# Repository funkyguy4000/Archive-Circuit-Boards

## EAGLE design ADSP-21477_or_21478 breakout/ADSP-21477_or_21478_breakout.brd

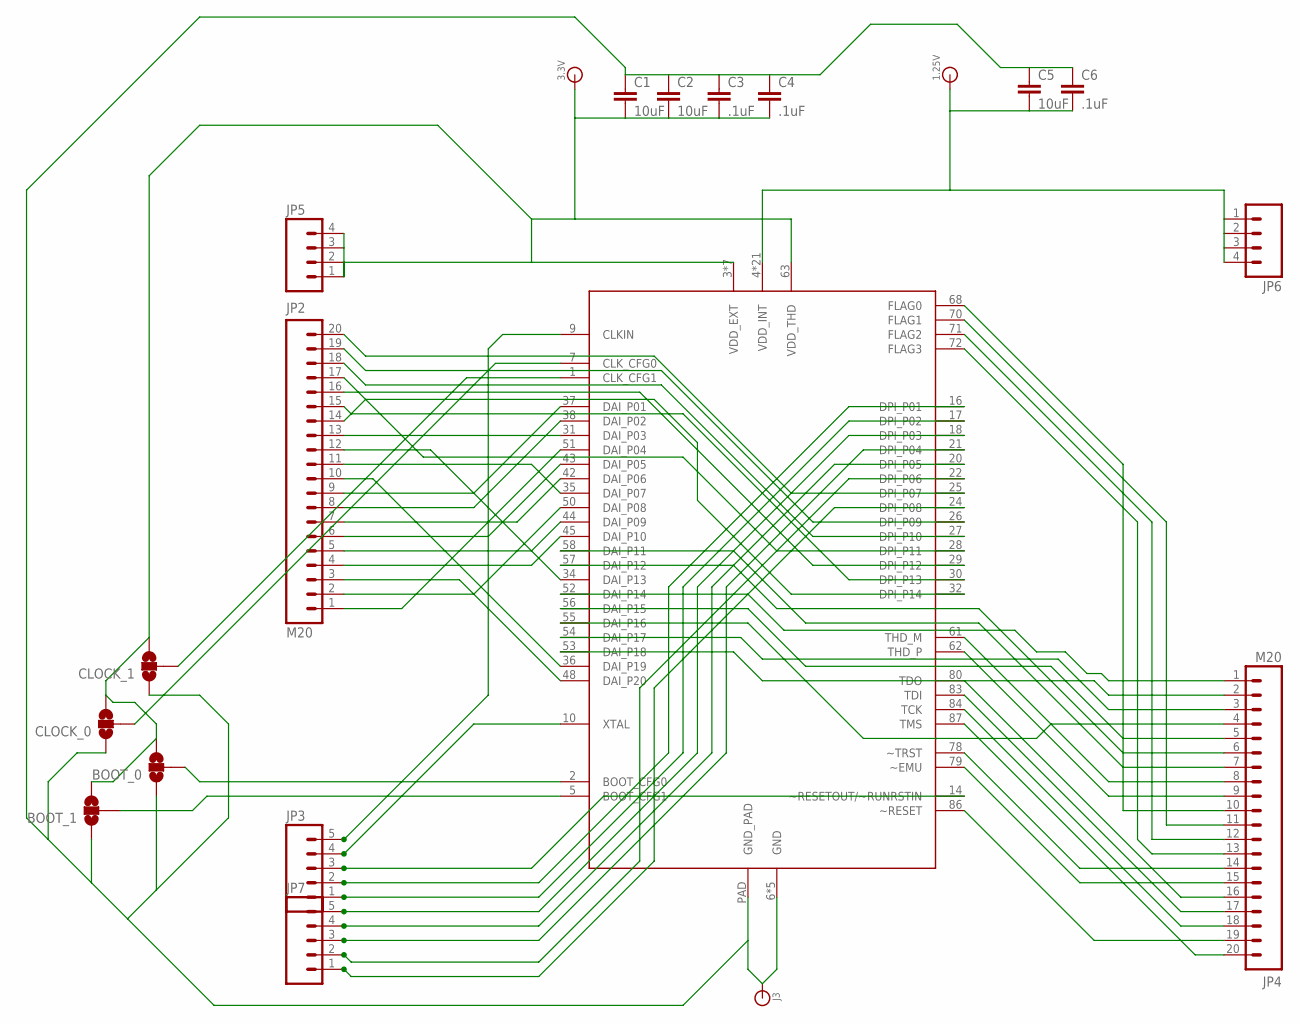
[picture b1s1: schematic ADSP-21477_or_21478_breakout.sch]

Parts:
1.25V, 3.3V: BANANA_CONN
BOOT_0, BOOT_1: SOLDERJUMPER_2WAYS; SJ_3
C1, C2, C5: 10uF; 0603-CAP
C3, C4, C6: .1uF; 0603-CAP
CLOCK_0, CLOCK_1: SOLDERJUMPER_2WAYS; SJ_3
J3: BANANA_CONN
JP2, JP4: M20; 1X20
JP3, JP7: M05PTH; 1X05
JP5, JP6: M04PTH; 1X04
U$1: ADSP-21479; QFN-88

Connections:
BOOT_CFG0: BOOT_0.2, U$1.2 (BOOT_CFG0)
BOOT_CFG1: BOOT_1.2, U$1.5 (BOOT_CFG1)
CLKIN: JP3.5, U$1.9 (CLKIN)
CLK_CFG0: CLOCK_0.2, U$1.7 (CLK_CFG0)
CLK_CFG1: CLOCK_1.2, U$1.1 (CLK_CFG1)
DAI_P01: JP2.9, U$1.37 (DAI_P01)
DAI_P02: JP2.8, U$1.38 (DAI_P02)
DAI_P03: JP2.13, U$1.31 (DAI_P03)
DAI_P04: JP2.1, U$1.51 (DAI_P04)
DAI_P05: JP2.6, U$1.43 (DAI_P05)
DAI_P06: JP2.7, U$1.42 (DAI_P06)
DAI_P07: JP2.11, U$1.35 (DAI_P07)
DAI_P08: JP2.2, U$1.50 (DAI_P08)
DAI_P09: JP2.5, U$1.44 (DAI_P09)
DAI_P10: JP2.4, U$1.45 (DAI_P10)
DAI_P11: JP4.7, U$1.58 (DAI_P11)
DAI_P12: JP4.6, U$1.57 (DAI_P12)
DAI_P13: JP2.12, U$1.34 (DAI_P13)
DAI_P14: JP4.1, U$1.52 (DAI_P14)
DAI_P15: JP4.5, U$1.56 (DAI_P15)
DAI_P16: JP4.4, U$1.55 (DAI_P16)
DAI_P17: JP4.3, U$1.54 (DAI_P17)
DAI_P18: JP4.2, U$1.53 (DAI_P18)
DAI_P19: JP2.10, U$1.36 (DAI_P19)
DAI_P20: JP2.3, U$1.48 (DAI_P20)
DPI_P01: JP3.2, U$1.16 (DPI_P01)
DPI_P02: JP3.1, U$1.17 (DPI_P02)
DPI_P03: JP7.5, U$1.18 (DPI_P03)
DPI_P04: JP7.3, U$1.21 (DPI_P04)
DPI_P05: JP7.4, U$1.20 (DPI_P05)
DPI_P06: JP7.2, U$1.22 (DPI_P06)
DPI_P07: JP2.20, U$1.25 (DPI_P07)
DPI_P08: JP7.1, U$1.24 (DPI_P08)
DPI_P09: JP2.19, U$1.26 (DPI_P09)
DPI_P10: JP2.18, U$1.27 (DPI_P10)
DPI_P11: JP2.17, U$1.28 (DPI_P11)
DPI_P12: JP2.16, U$1.29 (DPI_P12)
DPI_P13: JP2.15, U$1.30 (DPI_P13)
DPI_P14: JP2.14, U$1.32 (DPI_P14)
FLAG0: JP4.10, U$1.68 (FLAG0)
FLAG1: JP4.11, U$1.70 (FLAG1)
FLAG2: JP4.12, U$1.71 (FLAG2)
FLAG3: JP4.13, U$1.72 (FLAG3)
GND: BOOT_0.1, BOOT_1.1, C1.1, C2.1, C3.1, C4.1, C5.1, C6.1, CLOCK_0.1, CLOCK_1.1, J3.P$1, U$1.6 (GND), U$1.60 (GND), U$1.73 (GND), U$1.74 (GND), U$1.76 (GND), U$1.PAD (GND_PAD)
TCK: JP4.18, U$1.84 (TCK)
TDI: JP4.17, U$1.83 (TDI)
TDO: JP4.16, U$1.80 (TDO)
THD_M: JP4.8, U$1.61 (THD_M)
THD_P: JP4.9, U$1.62 (THD_P)
TMS: JP4.20, U$1.87 (TMS)
VDD_EXT+THD: 3.3V.P$1, BOOT_0.3, BOOT_1.3, C1.2, C2.2, C3.2, C4.2, CLOCK_0.3, CLOCK_1.3, JP5.1, JP5.2, JP5.3, JP5.4, U$1.3 (VDD_EXT), U$1.11 (VDD_EXT), U$1.23 (VDD_EXT), U$1.40 (VDD_EXT), U$1.47 (VDD_EXT), U$1.63 (VDD_THD), U$1.75 (VDD_EXT), U$1.81 (VDD_EXT)
VDD_INT: 1.25V.P$1, C5.2, C6.2, JP6.1, JP6.2, JP6.3, JP6.4, U$1.4 (VDD_INT), U$1.8 (VDD_INT), U$1.12 (VDD_INT), U$1.13 (VDD_INT), U$1.15 (VDD_INT), U$1.19 (VDD_INT), U$1.33 (VDD_INT), U$1.39 (VDD_INT), U$1.41 (VDD_INT), U$1.46 (VDD_INT), U$1.49 (VDD_INT), U$1.59 (VDD_INT), U$1.64 (VDD_INT), U$1.65 (VDD_INT), U$1.66 (VDD_INT), U$1.67 (VDD_INT), U$1.69 (VDD_INT), U$1.77 (VDD_INT), U$1.82 (VDD_INT), U$1.85 (VDD_INT), U$1.88 (VDD_INT)
XTAL: JP3.4, U$1.10 (XTAL)
~EMU: JP4.15, U$1.79 (~EMU)
~RESET: JP4.19, U$1.86 (~RESET)
~RESETOUT/~RUNRSTIN: JP3.3, U$1.14 (~RESETOUT/~RUNRSTIN)
~TRST: JP4.14, U$1.78 (~TRST)

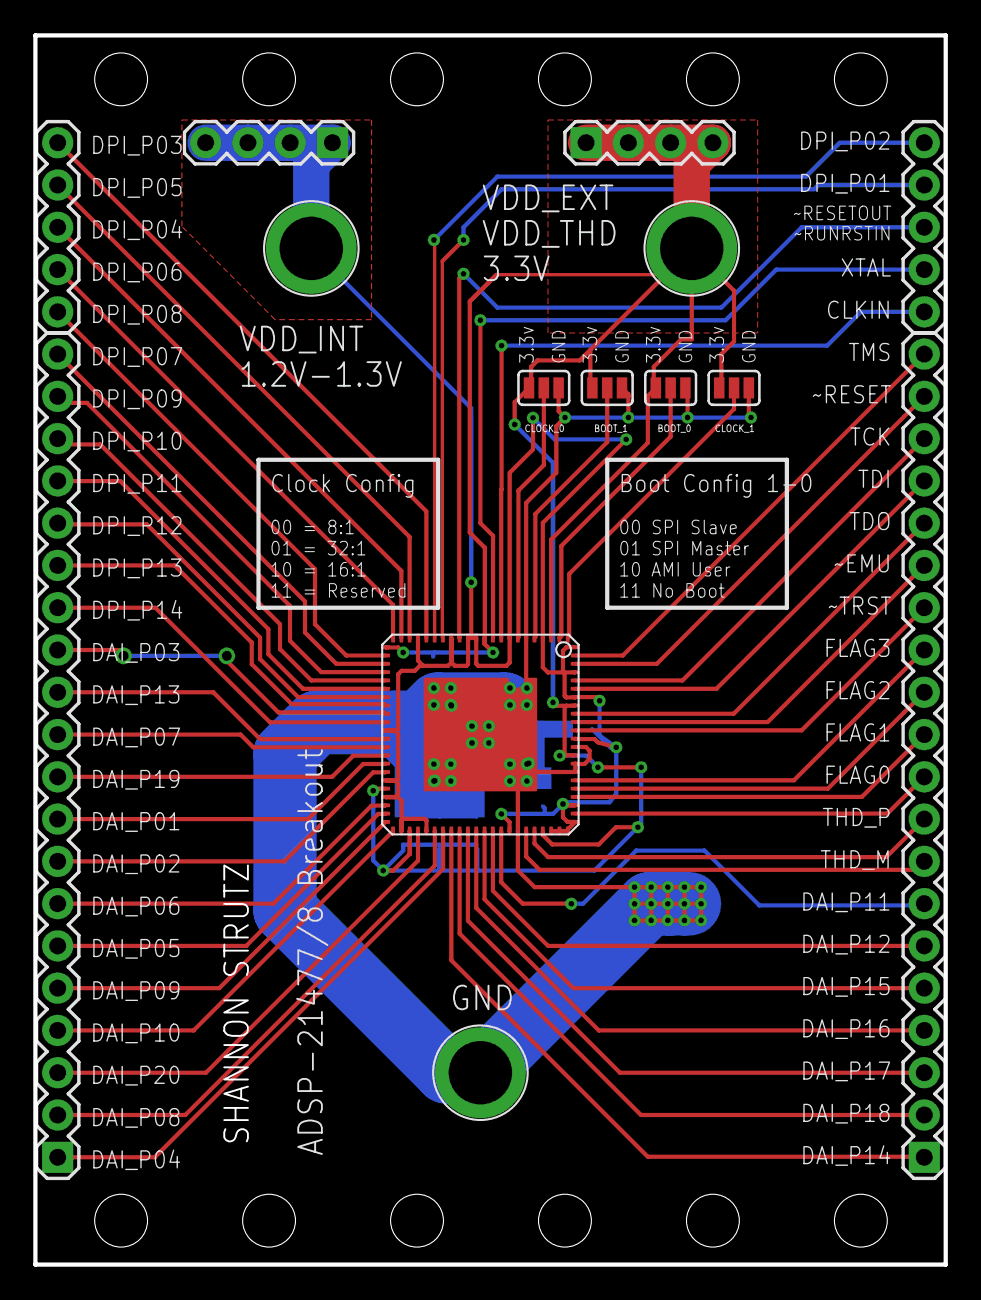
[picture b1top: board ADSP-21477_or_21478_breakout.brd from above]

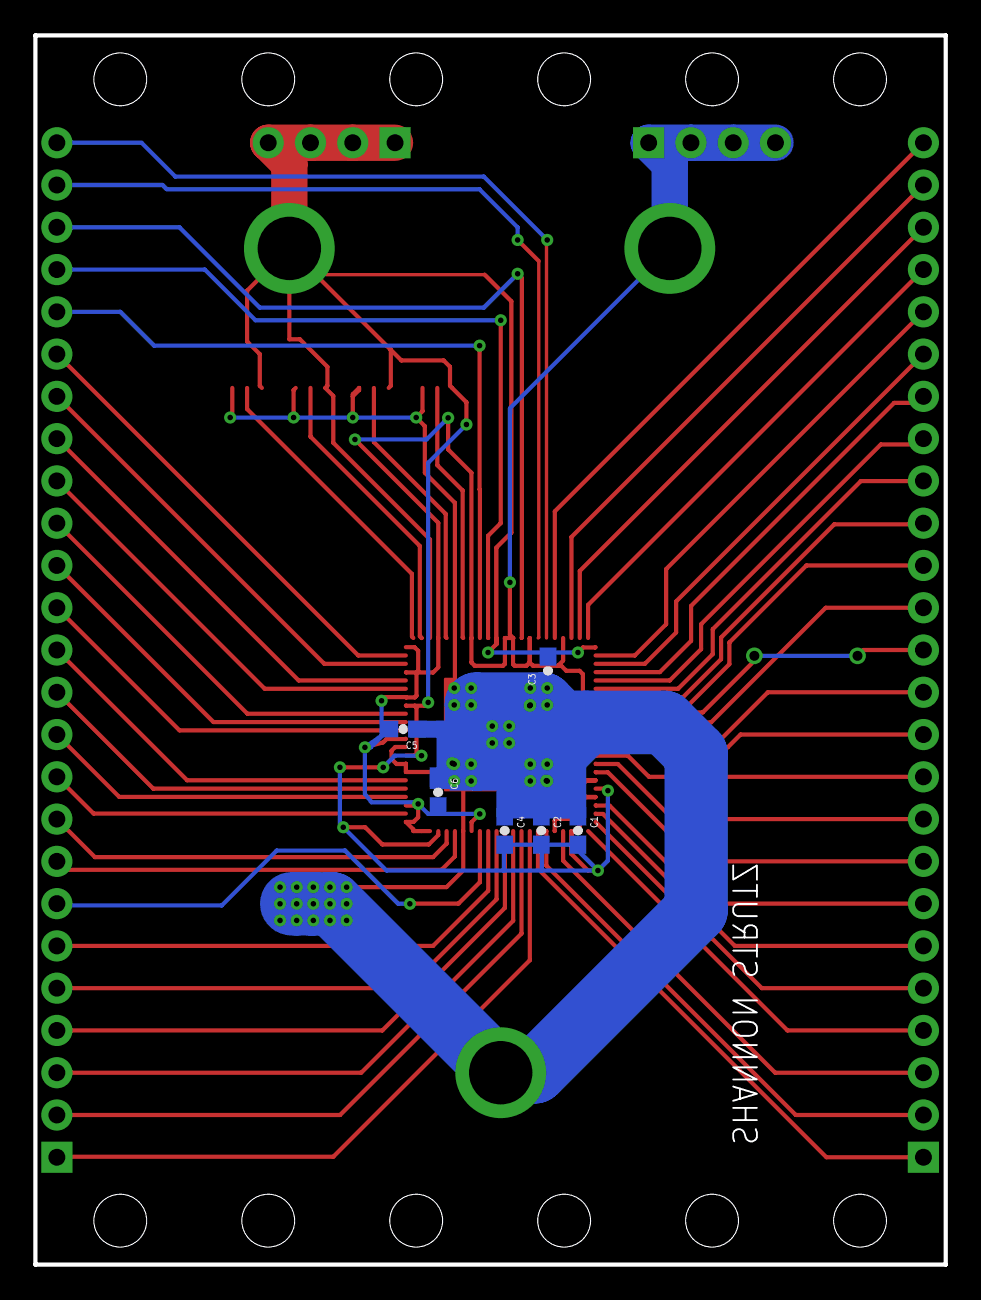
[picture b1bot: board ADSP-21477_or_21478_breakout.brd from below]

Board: 2 copper layers, 54.7 x 73.9 mm, 20 parts (6 on the bottom side), 57 nets.

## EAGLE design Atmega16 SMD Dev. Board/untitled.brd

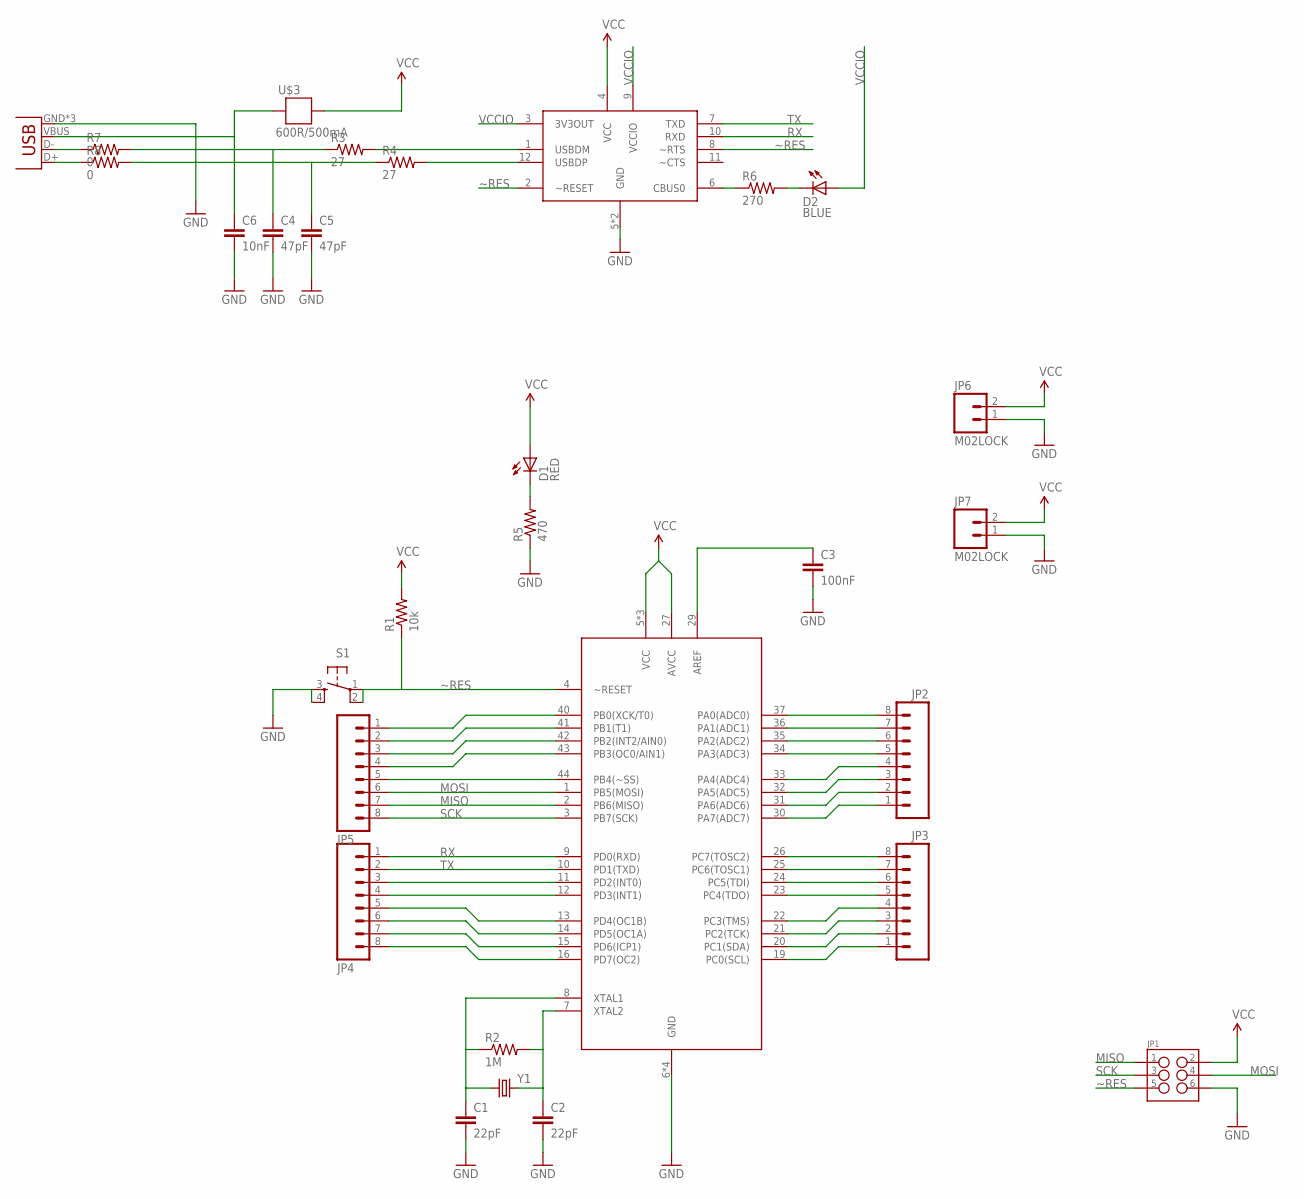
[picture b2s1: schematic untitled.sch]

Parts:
C1, C2: 22pF; 0603-CAP
C3: 100nF; 0603-CAP
C4, C5: 47pF; 0603-CAP
C6: 10nF; 0603-CAP
D1: RED; LED-0603
D2: BLUE; LED-0603
JP1: M03X2; 2X3_SMD
JP2, JP3, JP4, JP5: M081X08; 1X08
JP6, JP7: M02LOCK; 1X02_LOCK
R1: 10k; 0603-RES
R2: 1M; 0603-RES
R3, R4: 27; 0603-RES
R5: 470; 0603-RES
R6: 270; 0603-RES
R7, R8: 0; 0603-RES
S1: TAC_SWITCHSMD; TACTILE_SWITCH_SMD
U1: USB-MICROB
U$1: ATMEGA16QFP; 44-QFP_0.8
U$2: FTDI_FT234XD; DFN12-3X3
U$3: 600R/500mA; 0603
Y1: CRYSTAL10.5X4.8; CRYSTAL-SMD-10.5X4.8-2PIN

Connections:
D-: R7.1, U1.D-
D=: R8.1, U1.D+
GND: C1.2, C2.2, C3.2, C4.2, C5.2, C6.2, JP1.6, JP6.1, JP7.1, R5.1, S1.3, S1.4, U1.GND, U1.MT1 (GND), U1.MT2 (GND), U$1.6 (GND), U$1.18 (GND), U$1.28 (GND), U$1.39 (GND), U$2.5 (GND), U$2.PAD (GND)
MISO: JP1.1, JP5.7, U$1.2 (PB6(MISO))
MOSI: JP1.4, JP5.6, U$1.1 (PB5(MOSI))
unnamed: D1.C, R5.2
unnamed: C6.1, U1.VBUS, U$3.2
unnamed: C3.1, U$1.29 (AREF)
unnamed: R6.1, U$2.6 (CBUS0)
unnamed: D2.C, R6.2
PA0: JP2.8, U$1.37 (PA0(ADC0))
PA1: JP2.7, U$1.36 (PA1(ADC1))
PA2: JP2.6, U$1.35 (PA2(ADC2))
PA3: JP2.5, U$1.34 (PA3(ADC3))
PA4: JP2.4, U$1.33 (PA4(ADC4))
PA5: JP2.3, U$1.32 (PA5(ADC5))
PA6: JP2.2, U$1.31 (PA6(ADC6))
PA7: JP2.1, U$1.30 (PA7(ADC7))
PB0: JP5.1, U$1.40 (PB0(XCK/T0))
PB1: JP5.2, U$1.41 (PB1(T1))
PB2: JP5.3, U$1.42 (PB2(INT2/AIN0))
PB3: JP5.4, U$1.43 (PB3(OC0/AIN1))
PB4: JP5.5, U$1.44 (PB4(~SS))
PC2: JP3.3, U$1.21 (PC2(TCK))
PC3: JP3.4, U$1.22 (PC3(TMS))
PC4: JP3.5, U$1.23 (PC4(TDO))
PC5: JP3.6, U$1.24 (PC5(TDI))
PC6: JP3.7, U$1.25 (PC6(TOSC1))
PC7: JP3.8, U$1.26 (PC7(TOSC2))
PD2: JP4.3, U$1.11 (PD2(INT0))
PD3: JP4.4, U$1.12 (PD3(INT1))
PD4: JP4.5, U$1.13 (PD4(OC1B))
PD5: JP4.6, U$1.14 (PD5(OC1A))
PD6: JP4.7, U$1.15 (PD6(ICP1))
PD7: JP4.8, U$1.16 (PD7(OC2))
RX: JP4.1, U$1.9 (PD0(RXD)), U$2.10 (RXD)
SCK: JP1.3, JP5.8, U$1.3 (PB7(SCK))
SCL: JP3.1, U$1.19 (PC0(SCL))
SDA: JP3.2, U$1.20 (PC1(SDA))
TX: JP4.2, U$1.10 (PD1(TXD)), U$2.7 (TXD)
USBDR_N: C4.1, R3.1, R7.2
USBDR_P: C5.1, R4.1, R8.2
USB_N: R3.2, U$2.1 (USBDM)
USB_P: R4.2, U$2.12 (USBDP)
VCC: D1.A, JP1.2, JP6.2, JP7.2, R1.2, U$1.5 (VCC), U$1.17 (VCC), U$1.27 (AVCC), U$1.38 (VCC), U$2.4 (VCC), U$3.1
VCCIO: D2.A, U$2.3 (3V3OUT), U$2.9 (VCCIO)
XTAL1: C1.1, R2.1, U$1.8 (XTAL1), Y1.P$1 (1)
XTAL2: C2.1, R2.2, U$1.7 (XTAL2), Y1.P$2 (2)
~RES: JP1.5, R1.1, S1.1, S1.2, U$1.4 (~RESET), U$2.2 (~RESET), U$2.8 (~RTS)

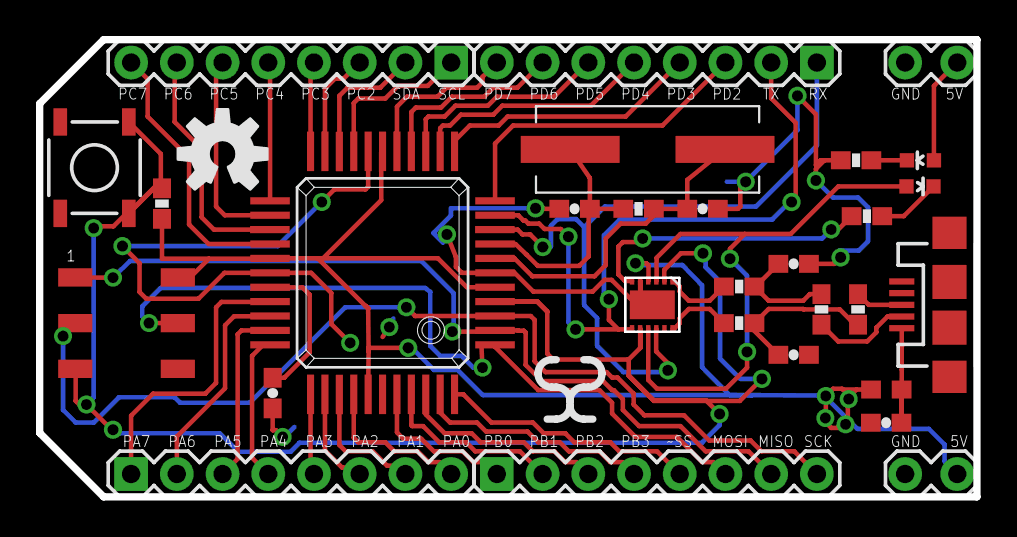
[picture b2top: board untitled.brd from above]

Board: 2 copper layers, 52.1 x 25.4 mm, 30 parts (0 on the bottom side), 49 nets.

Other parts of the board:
U$4: OSHW-LOGO-M

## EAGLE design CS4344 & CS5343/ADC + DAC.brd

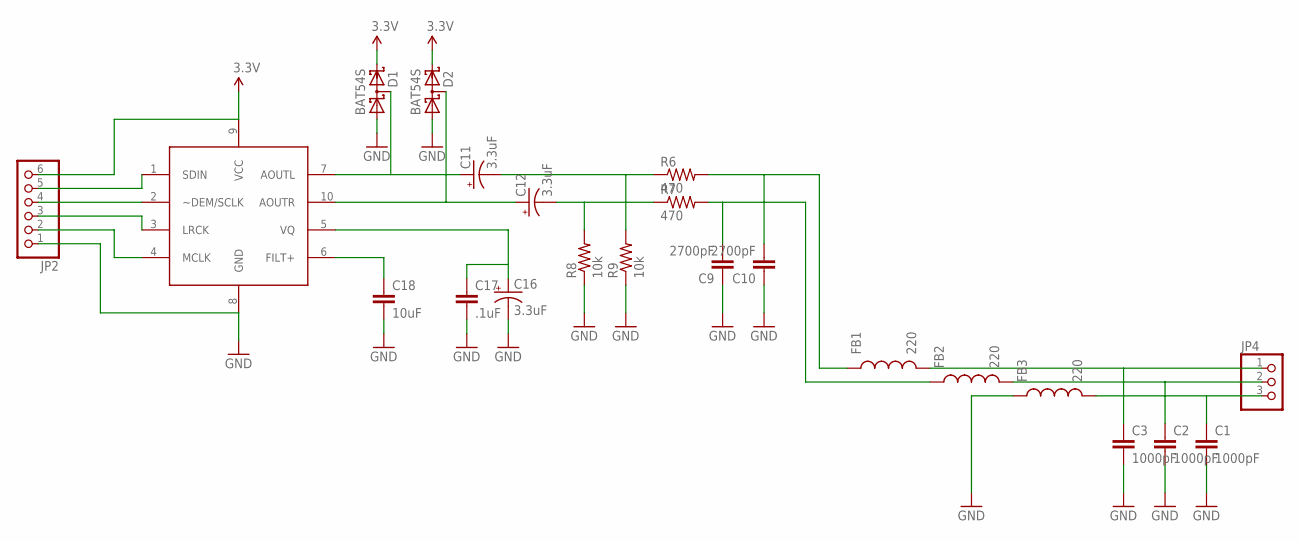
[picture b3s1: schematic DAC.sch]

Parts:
C1, C2, C3: 1000pF; 0402-CAP
C9, C10: 2700pF; 0402-CAP
C11, C12, C16: 3.3uF; EIA3216
C17: .1uF; 0402-CAP
C18: 10uF; 0402-CAP
D1, D2: BAT54S; SOT23
FB1, FB2, FB3: 220; 0805
JP2: PINHD-1X6; 1X06
JP4: PINHD-1X3; 1X03
R6, R7: 470; 0603-RES
R8, R9: 10k; 0603-RES
U$2: CS4344-DAC; TSSOP-10

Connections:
AOUTL: C3.1, FB1.2, JP4.1
AOUTL_C: C11.A (+), D1.3 (C1A2), U$2.7 (AOUTL)
AOUTL_FB: C10.2, FB1.1, R6.2
AOUTL_R: C11.C (-), R6.1, R9.2
AOUTR: C2.1, FB2.2, JP4.2
AOUTR_C: C12.A (+), D2.3 (C1A2), U$2.10 (AOUTR)
AOUTR_FB: C9.2, FB2.1, R7.2
AOUTR_R: C12.C (-), R7.1, R8.2
AOUTS: C1.1, FB3.2, JP4.3
FILT+: C18.1, U$2.6 (FILT+)
GND: C1.2, C2.2, C3.2, C9.1, C10.1, C16.C (-), C17.2, C18.2, D1.1 (A1), D2.1 (A1), FB3.1, JP2.1, R8.1, R9.1, U$2.8 (GND); also elsewhere on the board
LRCLK: JP2.3, U$2.3 (LRCK)
MCLK: JP2.2, U$2.4 (MCLK)
SCLK: JP2.4, U$2.2 (~DEM/SCLK)
SDIN: JP2.5, U$2.1 (SDIN)
VCC: D1.2 (C2), D2.2 (C2), JP2.6, U$2.9 (VCC); also elsewhere on the board
VQ: C16.A (+), C17.1, U$2.5 (VQ)

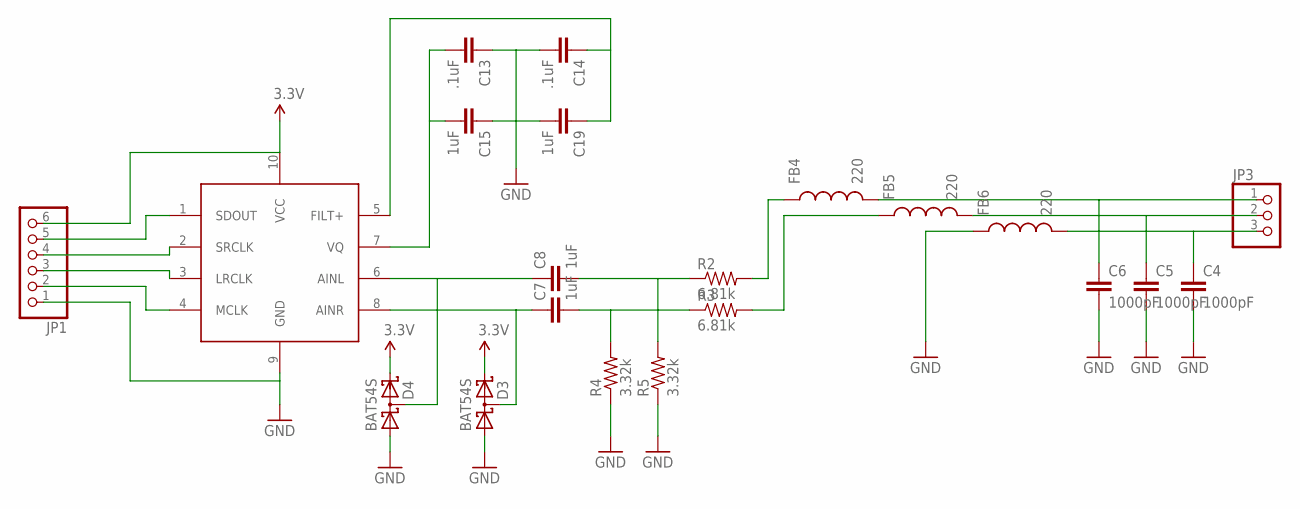
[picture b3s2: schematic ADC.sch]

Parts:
C4, C5, C6: 1000pF; 0402-CAP
C7, C8, C15, C19: 1uF; 0402-CAP
C13, C14: .1uF; 0402-CAP
D3, D4: BAT54S; SOT23
FB4, FB5, FB6: 220; 0805
JP1: PINHD-1X6; 1X06
JP3: PINHD-1X3; 1X03
R2, R3: 6.81k; 0603-RES
R4, R5: 3.32k; 0603-RES
U$3: CS5343; TSSOP-10

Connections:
AINL: C6.1, FB4.2, JP3.1
AINL_C: C8.1, D4.3 (C1A2), U$3.6 (AINL)
AINL_FB: FB4.1, R2.2
AINL_R: C8.2, R2.1, R5.2
AINR: C5.1, FB5.2, JP3.2
AINR_C: C7.1, D3.3 (C1A2), U$3.8 (AINR)
AINR_FB: FB5.1, R3.2
AINR_R: C7.2, R3.1, R4.2
AIN_SLEEV: C4.1, FB6.2, JP3.3
GND: C4.2, C5.2, C6.2, C13.1, C14.2, C15.1, C19.2, D3.1 (A1), D4.1 (A1), FB6.1, JP1.1, R4.1, R5.1, U$3.9 (GND); also elsewhere on the board
unnamed: C13.2, C15.2, U$3.7 (VQ)
unnamed: JP1.2, U$3.4 (MCLK)
unnamed: C14.1, C19.1, U$3.5 (FILT+)
unnamed: JP1.3, U$3.3 (LRCLK)
unnamed: JP1.4, U$3.2 (SRCLK)
unnamed: JP1.5, U$3.1 (SDOUT)
VCC: D3.2 (C2), D4.2 (C2), JP1.6, U$3.10 (VCC); also elsewhere on the board

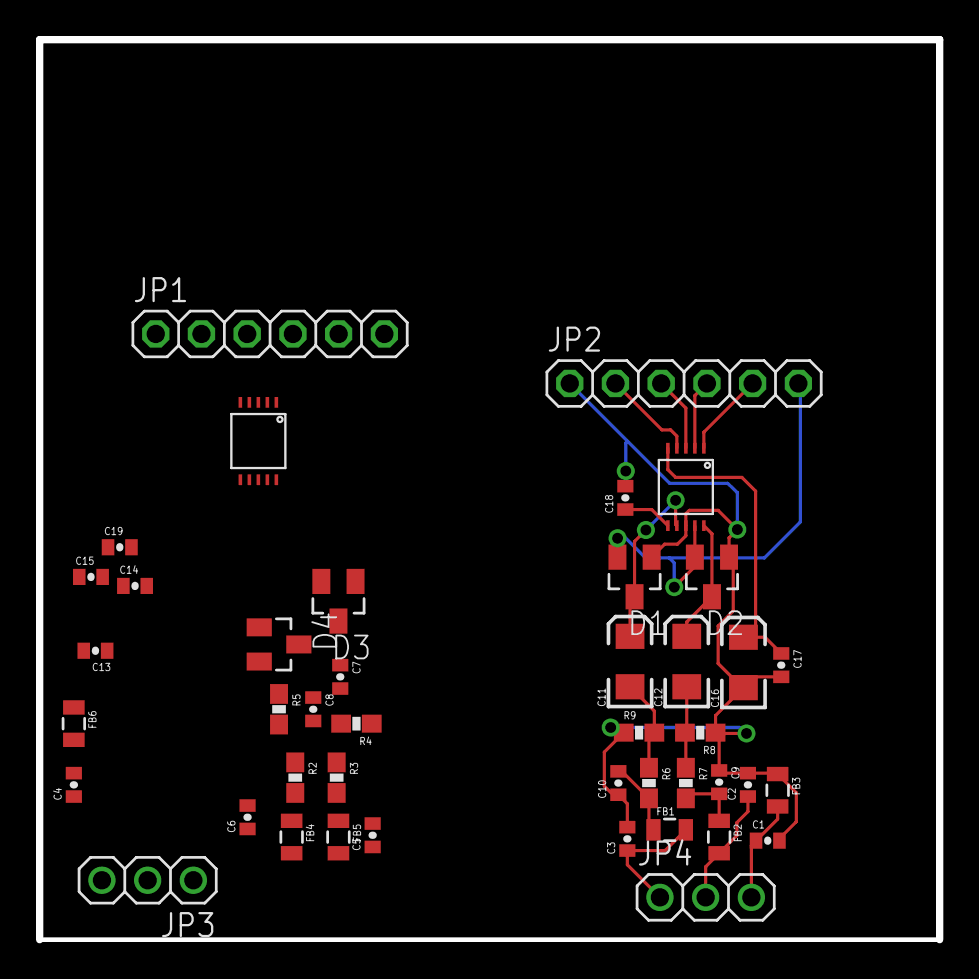
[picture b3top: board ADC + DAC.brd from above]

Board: 2 copper layers, 50.0 x 50.0 mm, 43 parts (0 on the bottom side), 32 nets.

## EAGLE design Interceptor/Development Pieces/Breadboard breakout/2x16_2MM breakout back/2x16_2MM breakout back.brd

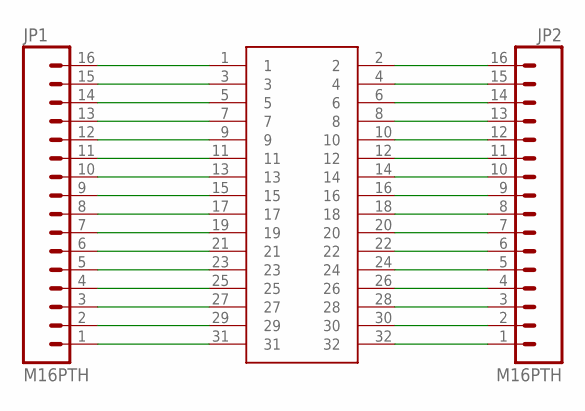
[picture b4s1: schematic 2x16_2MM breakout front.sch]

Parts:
JP1, JP2: M16PTH; 1X16
U$1: 2X16_2MM_SMD

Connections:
unnamed: JP1.16, U$1.1
unnamed: JP1.15, U$1.3
unnamed: JP1.14, U$1.5
unnamed: JP1.13, U$1.7
unnamed: JP1.12, U$1.9
unnamed: JP1.11, U$1.11
unnamed: JP1.10, U$1.13
unnamed: JP1.9, U$1.15
unnamed: JP1.8, U$1.17
unnamed: JP1.7, U$1.19
unnamed: JP1.6, U$1.21
unnamed: JP1.5, U$1.23
unnamed: JP1.4, U$1.25
unnamed: JP1.3, U$1.27
unnamed: JP1.2, U$1.29
unnamed: JP1.1, U$1.31
unnamed: JP2.1, U$1.32
unnamed: JP2.2, U$1.30
unnamed: JP2.3, U$1.28
unnamed: JP2.4, U$1.26
unnamed: JP2.5, U$1.24
unnamed: JP2.6, U$1.22
unnamed: JP2.7, U$1.20
unnamed: JP2.8, U$1.18
unnamed: JP2.9, U$1.16
unnamed: JP2.10, U$1.14
unnamed: JP2.11, U$1.12
unnamed: JP2.12, U$1.10
unnamed: JP2.13, U$1.8
unnamed: JP2.14, U$1.6
unnamed: JP2.15, U$1.4
unnamed: JP2.16, U$1.2

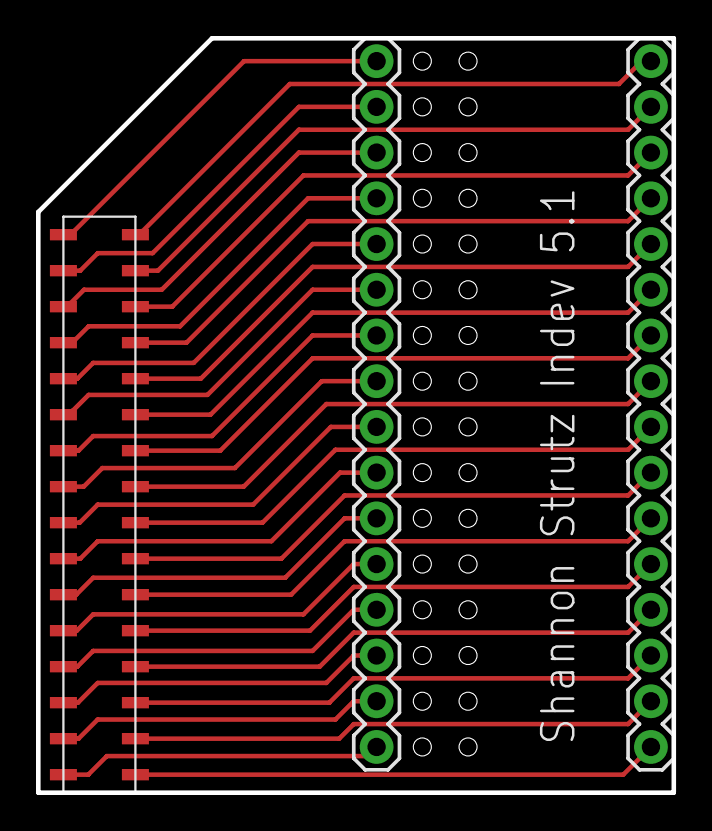
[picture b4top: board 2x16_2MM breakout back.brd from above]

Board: 2 copper layers, 35.3 x 41.9 mm, 3 parts (0 on the bottom side), 32 nets.

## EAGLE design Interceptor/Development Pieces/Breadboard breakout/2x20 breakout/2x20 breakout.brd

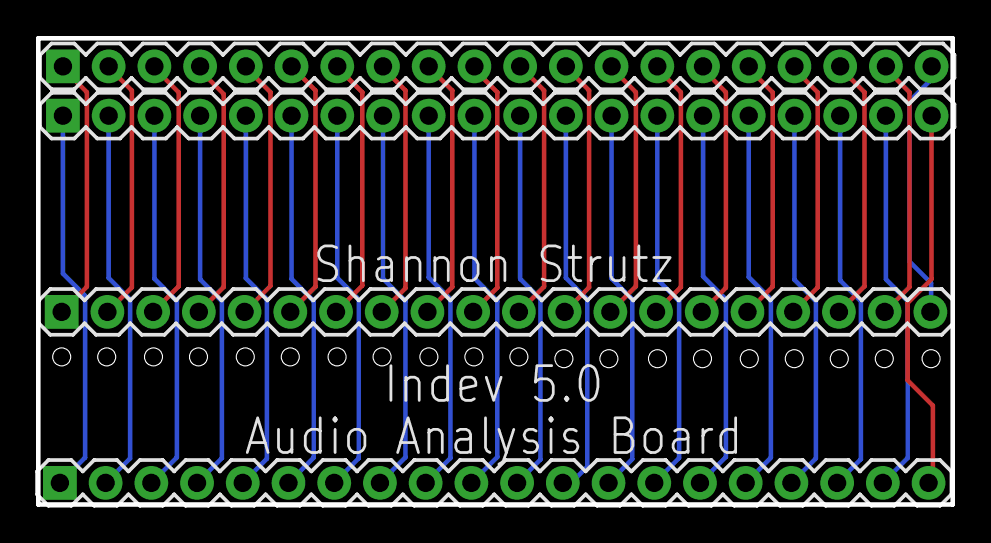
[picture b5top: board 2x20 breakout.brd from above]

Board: 2 copper layers, 50.8 x 25.9 mm, 4 parts (0 on the bottom side), 40 nets.

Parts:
JP1, JP2, JP3, JP4: M20; 1X20

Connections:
unnamed: JP2.1, JP4.1
unnamed: JP2.2, JP4.2
unnamed: JP2.3, JP4.3
unnamed: JP2.4, JP4.4
unnamed: JP2.5, JP4.5
unnamed: JP2.6, JP4.6
unnamed: JP2.7, JP4.7
unnamed: JP2.8, JP4.8
unnamed: JP2.9, JP4.9
unnamed: JP2.10, JP4.10
unnamed: JP2.11, JP4.11
unnamed: JP2.12, JP4.12
unnamed: JP2.13, JP4.13
unnamed: JP2.14, JP4.14
unnamed: JP2.15, JP4.15
unnamed: JP2.16, JP4.16
unnamed: JP2.17, JP4.17
unnamed: JP2.18, JP4.18
unnamed: JP2.19, JP4.19
unnamed: JP2.20, JP4.20
unnamed: JP1.1, JP3.1
unnamed: JP1.2, JP3.2
unnamed: JP1.3, JP3.3
unnamed: JP1.4, JP3.4
unnamed: JP1.5, JP3.5
unnamed: JP1.6, JP3.6
unnamed: JP1.7, JP3.7
unnamed: JP1.8, JP3.8
unnamed: JP1.9, JP3.9
unnamed: JP1.10, JP3.10
unnamed: JP1.11, JP3.11
unnamed: JP1.12, JP3.12
unnamed: JP1.13, JP3.13
unnamed: JP1.14, JP3.14
unnamed: JP1.15, JP3.15
unnamed: JP1.16, JP3.16
unnamed: JP1.17, JP3.17
unnamed: JP1.18, JP3.18
unnamed: JP1.19, JP3.19
unnamed: JP1.20, JP3.20

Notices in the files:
parts and their libraries:
SparkFun-Connectors: Licensing: CC v3.0 Share-Alike You are welcome to use this library for commercial purposes.
